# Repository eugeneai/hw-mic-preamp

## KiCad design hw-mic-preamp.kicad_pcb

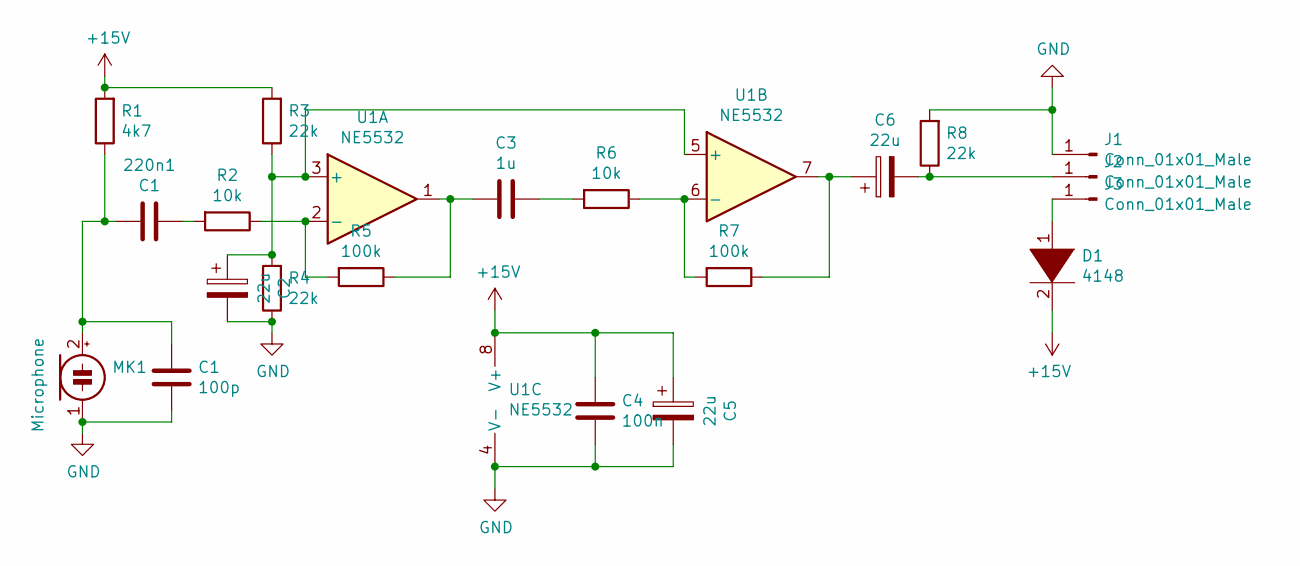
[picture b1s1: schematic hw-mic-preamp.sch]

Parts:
220n1: C1; C_0805_2012Metric_Pad1.18x1.45mm_HandSolder
C1: 100p; C_0805_2012Metric_Pad1.18x1.45mm_HandSolder
C2, C5, C6: 22u; CP_Radial_D4.0mm_P2.00mm
C3: 1u; C_0805_2012Metric_Pad1.18x1.45mm_HandSolder
C4: 100n; C_0805_2012Metric_Pad1.18x1.45mm_HandSolder
D1: 4148; D_0805_2012Metric_Pad1.15x1.40mm_HandSolder
J1, J2, J3: Conn_01x01_Male; SolderWirePad_1x01_SMD_1x2mm
MK1: Microphone; PinHeader_1x02_P2.54mm_Vertical
R1: 4k7; R_0805_2012Metric_Pad1.20x1.40mm_HandSolder
R2, R6: 10k; R_0805_2012Metric_Pad1.20x1.40mm_HandSolder
R3, R4, R8: 22k; R_0805_2012Metric_Pad1.20x1.40mm_HandSolder
R5, R7: 100k; R_0805_2012Metric_Pad1.20x1.40mm_HandSolder
U1: NE5532; SO-8_3.9x4.9mm_P1.27mm

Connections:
+15V: C4.2, C5.1, D1.2 (A), R1.2, R3.2, U1.8 (V+)
GND: C1.1, C2.2, C4.1, C5.2, J1.1, MK1.1 (-), R4.1, R8.2, U1.4 (V-)
unnamed: 220n1.1, R2.2
unnamed: 220n1.2, C1.2, MK1.2 (+), R1.1
unnamed: C2.1, R3.1, R4.2, U1.3 (+), U1.5 (+)
unnamed: C3.1, R6.2
unnamed: C3.2, R5.1, U1.1
unnamed: C6.1, R7.1, U1.7
unnamed: C6.2, J2.1, R8.1
unnamed: D1.1 (K), J3.1
unnamed: R2.1, R5.2, U1.2 (-)
unnamed: R6.1, R7.2, U1.6 (-)

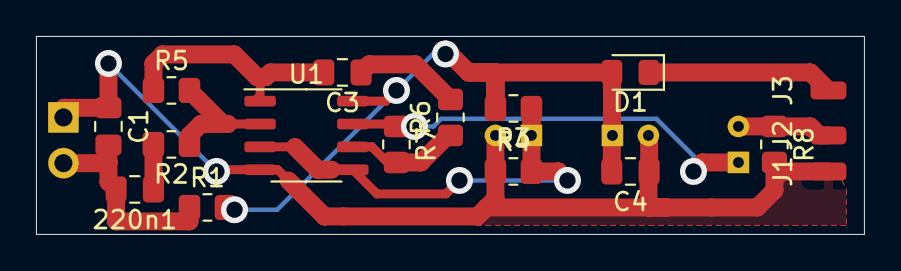
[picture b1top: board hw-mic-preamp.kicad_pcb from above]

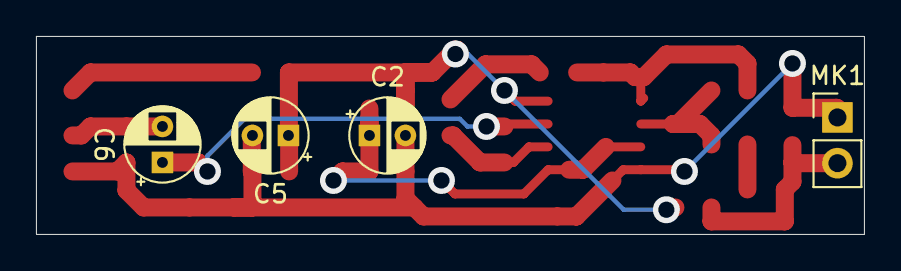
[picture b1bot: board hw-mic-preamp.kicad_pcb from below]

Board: 2 copper layers, 46.0 x 11.0 mm, 21 parts (4 on the bottom side), 12 nets.

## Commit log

2021-04-04 Initial import
